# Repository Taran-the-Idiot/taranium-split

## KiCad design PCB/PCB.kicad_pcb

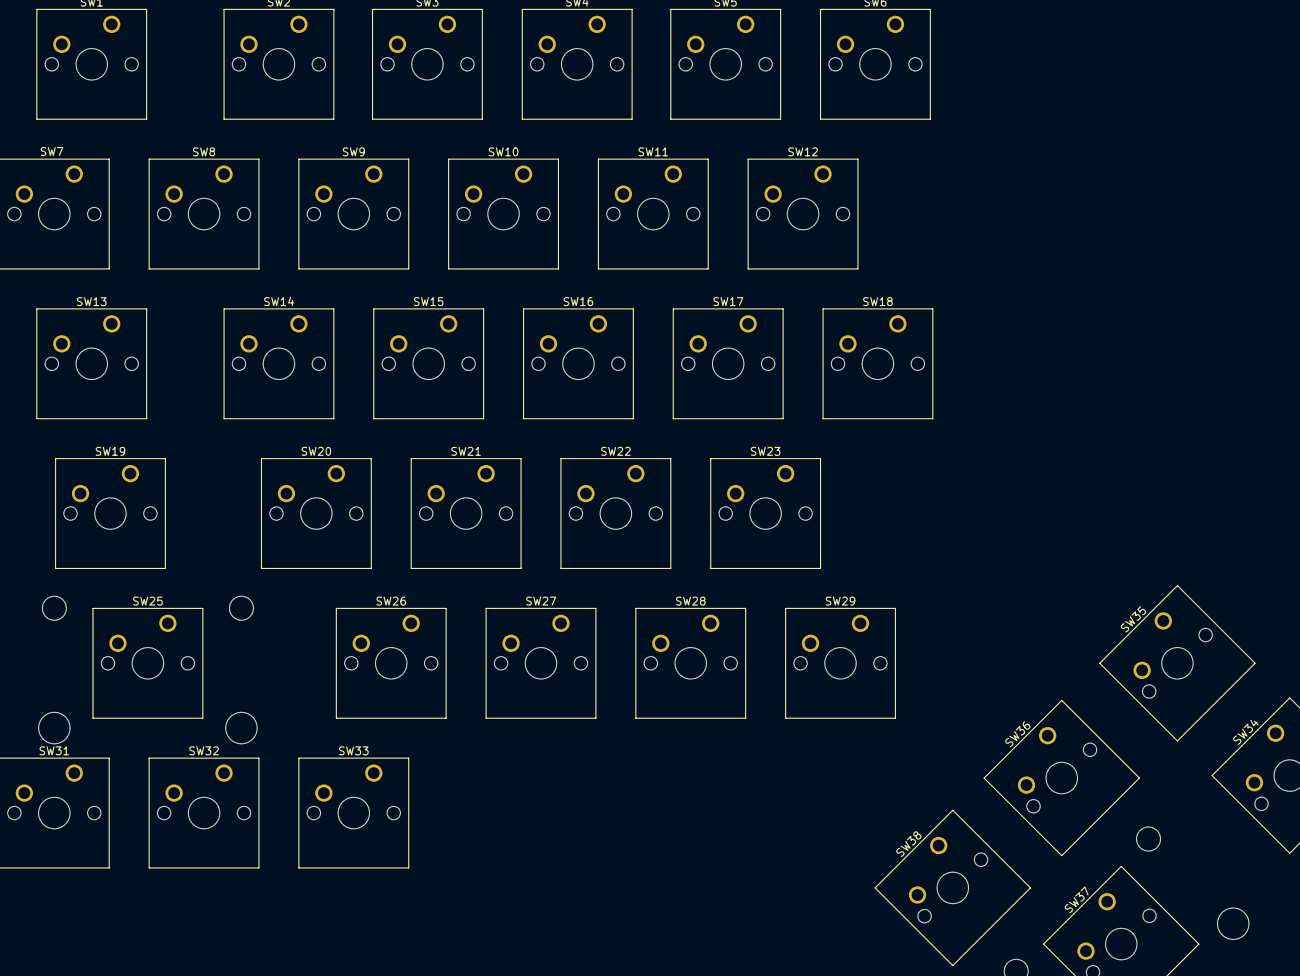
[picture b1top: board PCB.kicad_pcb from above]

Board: 2 copper layers, 36 parts (0 on the bottom side), 7 nets, no tracks yet.

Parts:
SW1, SW13: SW_Push; SW_Cherry_MX_1.50u_PCB
SW2, SW3, SW4, SW5, SW6, SW7, SW8, SW9, SW10, SW11, SW12, SW14, SW15, SW16, SW17, SW18, SW20, SW21, SW22, SW23, SW26, SW27, SW28, SW29, SW31, SW32, SW33, SW34, SW35, SW36, SW38: SW_Push; SW_Cherry_MX_1.00u_PCB
SW19: SW_Push; SW_Cherry_MX_1.75u_PCB
SW25: SW_Push; SW_Cherry_MX_2.25u_PCB
SW37: SW_Push; SW_Cherry_MX_2.00u_PCB

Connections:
/Col0: SW1.2, SW7.2, SW13.2, SW19.2, SW25.2, SW31.2
/Col1: SW2.2, SW8.2, SW14.2, SW20.2, SW26.2, SW32.2
/Col2: SW3.2, SW9.2, SW15.2, SW21.2, SW27.2, SW33.2
/Col3: SW4.2, SW10.2, SW16.2, SW22.2, SW28.2
/Col4: SW5.2, SW11.2, SW17.2, SW23.2, SW29.2
/Col5: SW6.2, SW12.2, SW18.2
/Col7: SW34.2, SW35.2, SW36.2, SW37.2, SW38.2
